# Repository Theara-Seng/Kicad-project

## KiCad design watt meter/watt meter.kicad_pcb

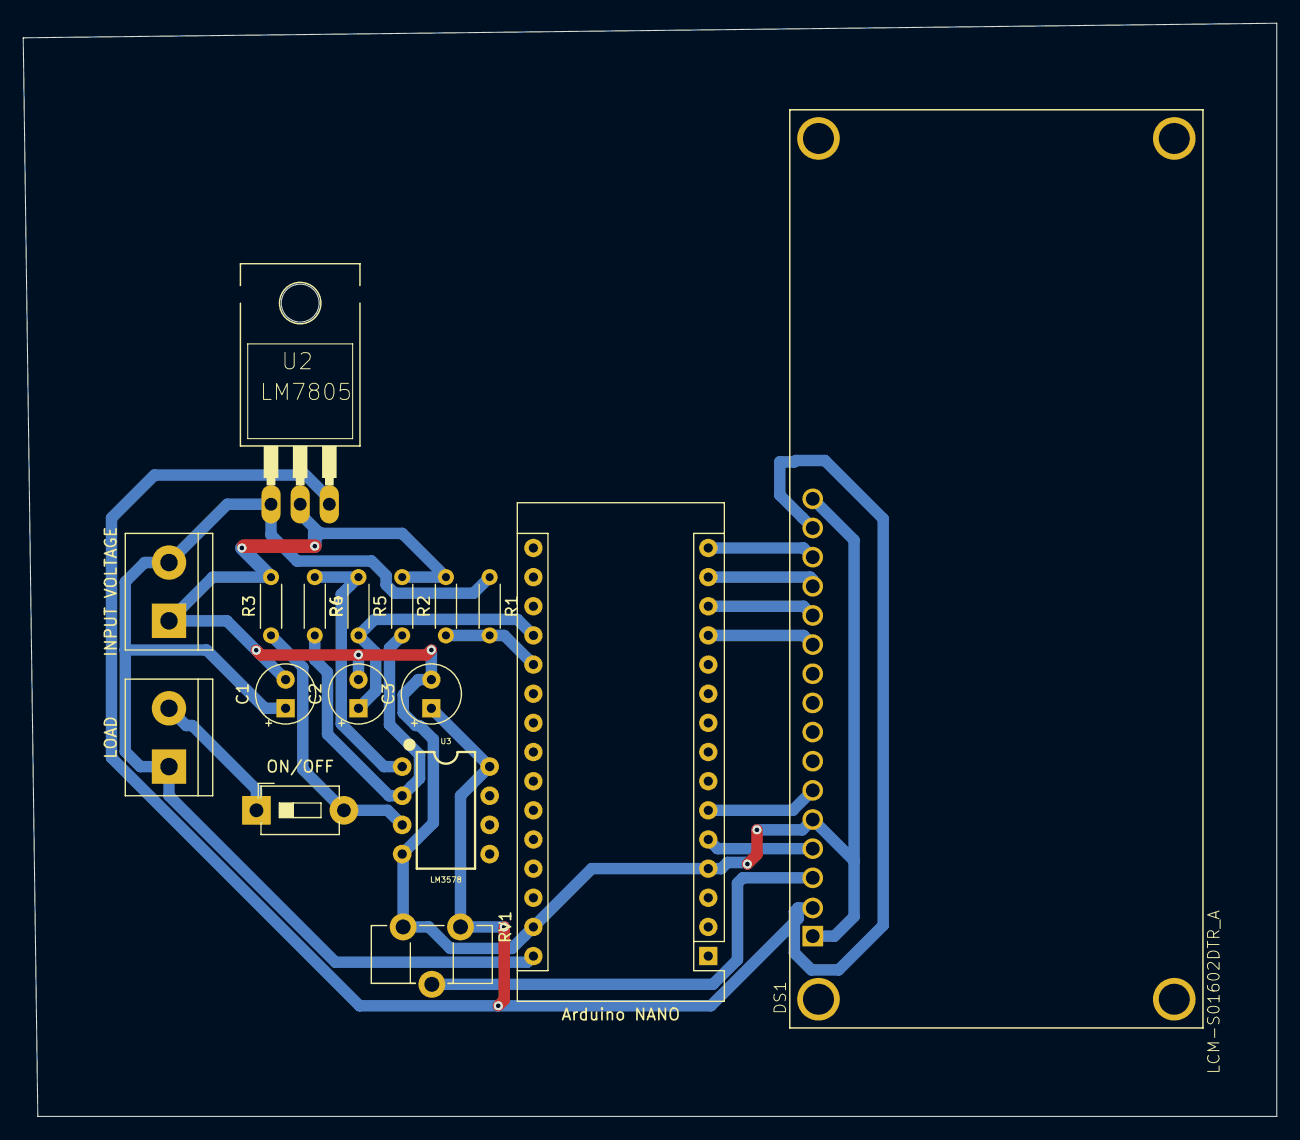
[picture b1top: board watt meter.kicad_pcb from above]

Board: 2 copper layers, 109.2 x 95.2 mm, 17 parts (0 on the bottom side), 16 nets.

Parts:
Arduino NANO: Arduino_Nano_v3.x; Arduino_Nano
C1, C2, C3: C; CP_Radial_Tantal_D5.0mm_P2.50mm
DS1: LCM-S01602DTR_A; LCD_LCM-S01602DTR%2fA
INPUT VOLTAGE: Conn_01x02_Female; TerminalBlock_bornier-2_P5.08mm
LOAD: Conn_01x02_Female; TerminalBlock_bornier-2_P5.08mm
ON/OFF: SW_DIP_x01; SW_DIP_SPSTx01_Slide_6.7x4.1mm_W7.62mm_P2.54mm_LowProfile
R1, R2, R3, R4, R5, R6: R; R_Axial_DIN0204_L3.6mm_D1.6mm_P5.08mm_Horizontal
RV1: R_POT; Potentiometer_Piher_PT-10-H05_Horizontal
U2: LM7805; TO220
U3: LM3578; DIP08

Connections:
/A0: Arduino NANO.19, C2.1, R6.1
/A1: Arduino NANO.20, R1.2, R2.1
/D2: Arduino NANO.5, DS1.4
/D3: Arduino NANO.6, DS1.6
/D9: Arduino NANO.12, DS1.11
/D10: Arduino NANO.13, DS1.12
/D11: Arduino NANO.14, DS1.13
/D12: Arduino NANO.15, DS1.14
/GND: Arduino NANO.4, Arduino NANO.29, C1.2, C2.2, C3.2, DS1.1, DS1.5, DS1.16, INPUT VOLTAGE.1, R2.2, R3.2, R5.2, RV1.3, U2.2, U3.4
/V5: C3.1, DS1.2, DS1.15, RV1.1, U2.3, U3.8
/V12: Arduino NANO.30, C1.1, INPUT VOLTAGE.2, LOAD.1, R1.1, U2.1
unnamed: DS1.3, RV1.2
unnamed: LOAD.2, ON/OFF.1
unnamed: ON/OFF.2, R3.1, U3.3
unnamed: R4.1, R6.2, U3.1
unnamed: R4.2, R5.1, U3.2
